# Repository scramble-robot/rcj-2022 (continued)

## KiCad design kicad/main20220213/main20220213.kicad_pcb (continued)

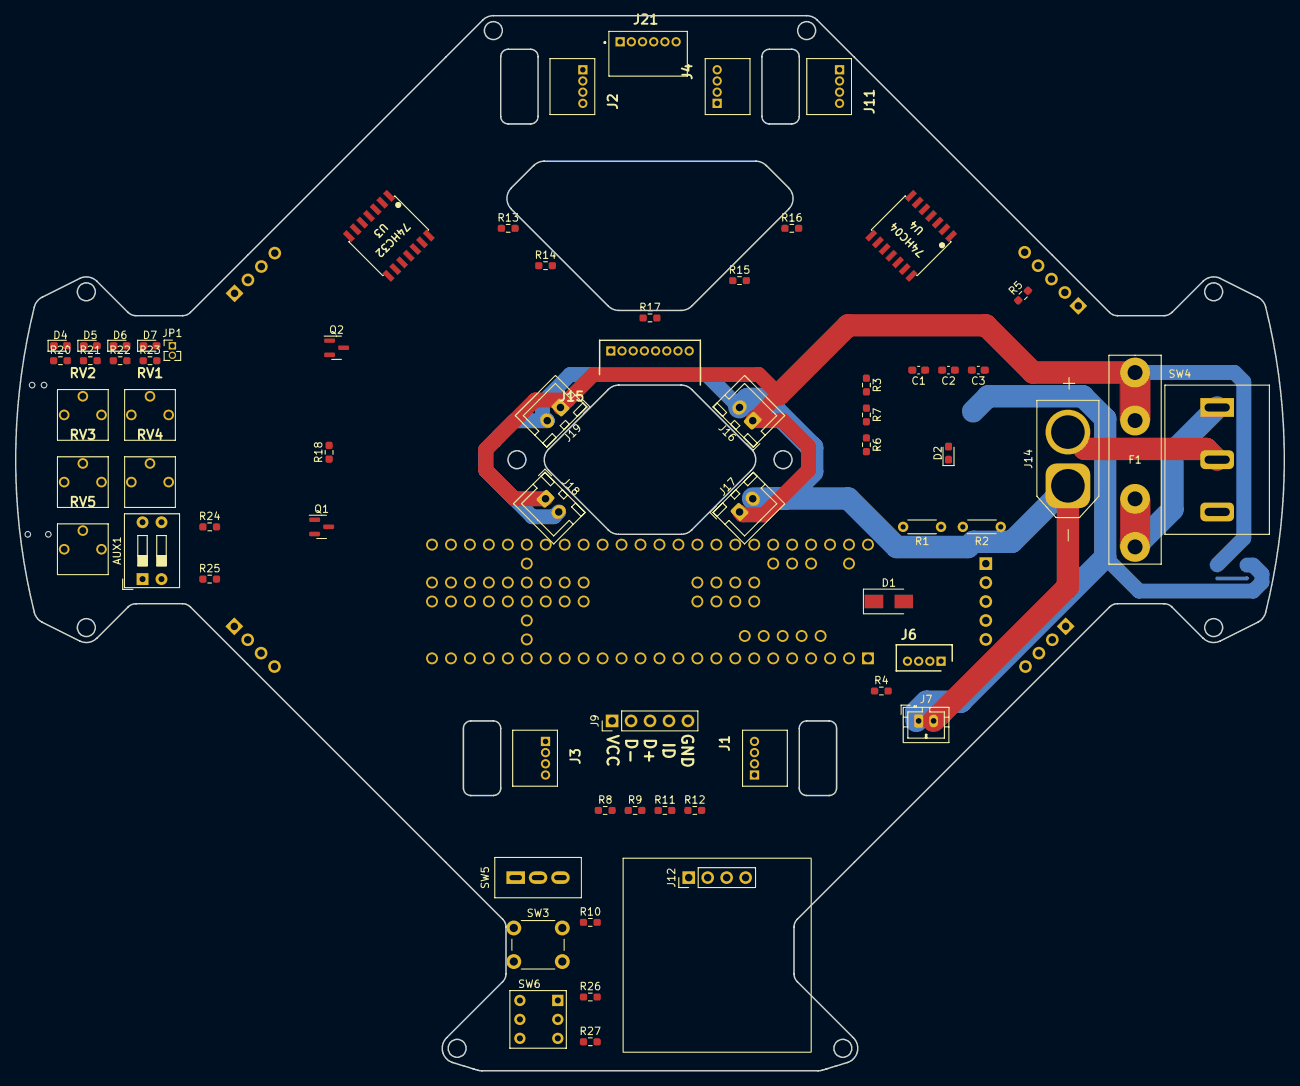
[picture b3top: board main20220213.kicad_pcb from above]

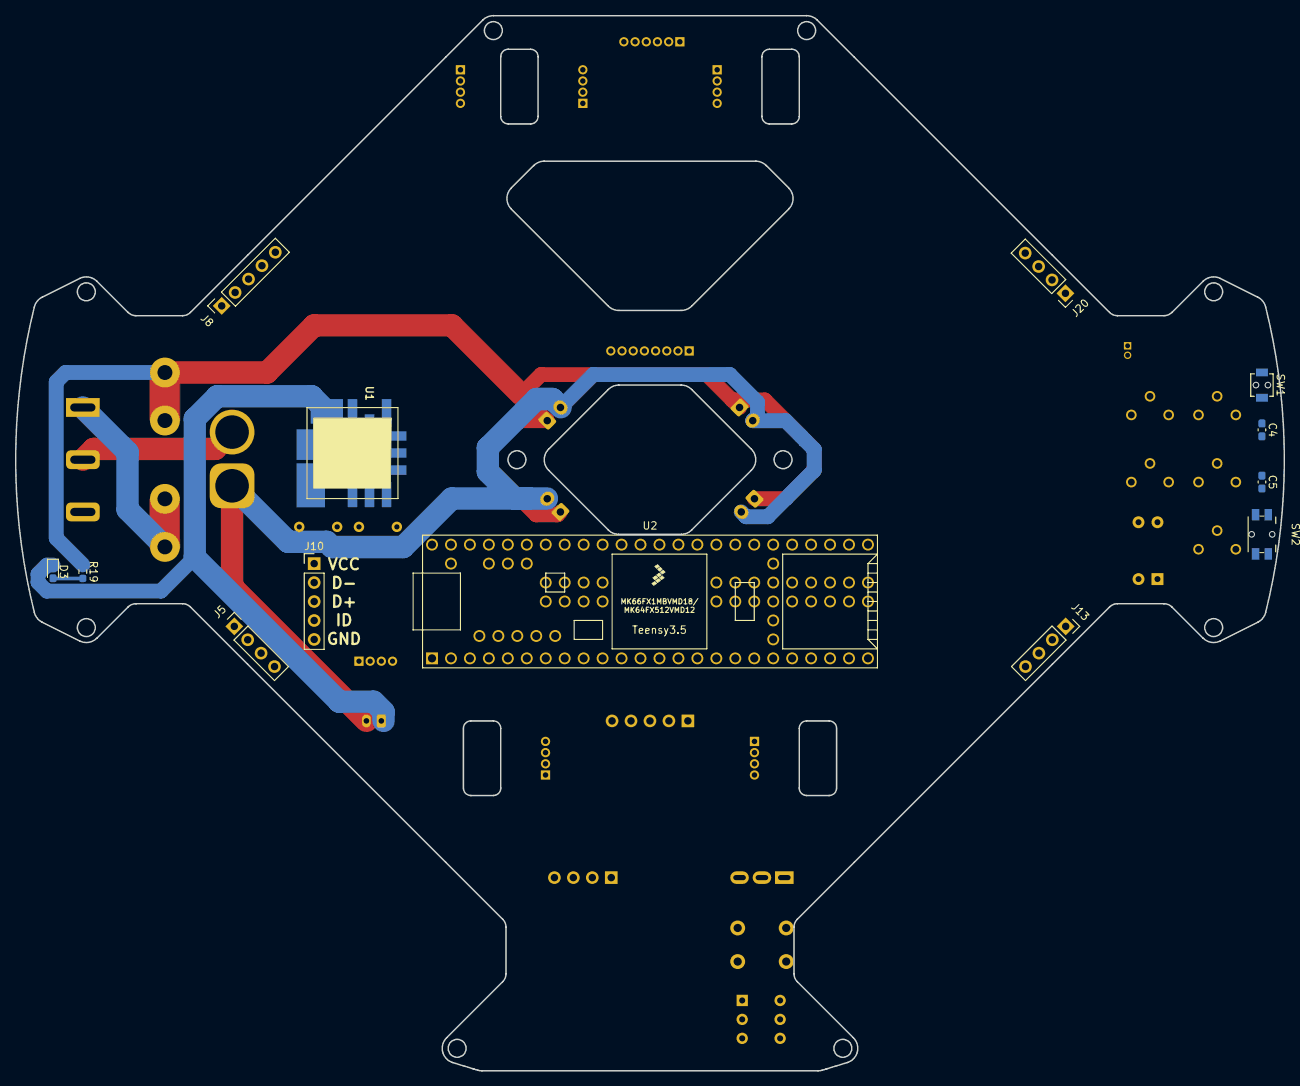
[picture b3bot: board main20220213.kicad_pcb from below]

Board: 2 copper layers, 170.0 x 141.4 mm, 80 parts (13 on the bottom side), 89 nets.

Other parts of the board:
D4: LED1_R; LED_SMLE13WBC8W1
D5: LED2_G; LED_SMLE13WBC8W1
R20, R21, R22, R23: 120; R_0603_1608Metric_Pad0.98x0.95mm_HandSolder

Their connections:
/LED/LED1: R20.1; also elsewhere on the board
/LED/LED2: R21.1; also elsewhere on the board
/LED/LED3: R22.1; also elsewhere on the board
/LED/LED4: R23.1; also elsewhere on the board
unnamed 16: D4.1 (K), D5.1 (K); also elsewhere on the board
unnamed: D4.2 (A), R20.2
unnamed: D5.2 (A), R21.2

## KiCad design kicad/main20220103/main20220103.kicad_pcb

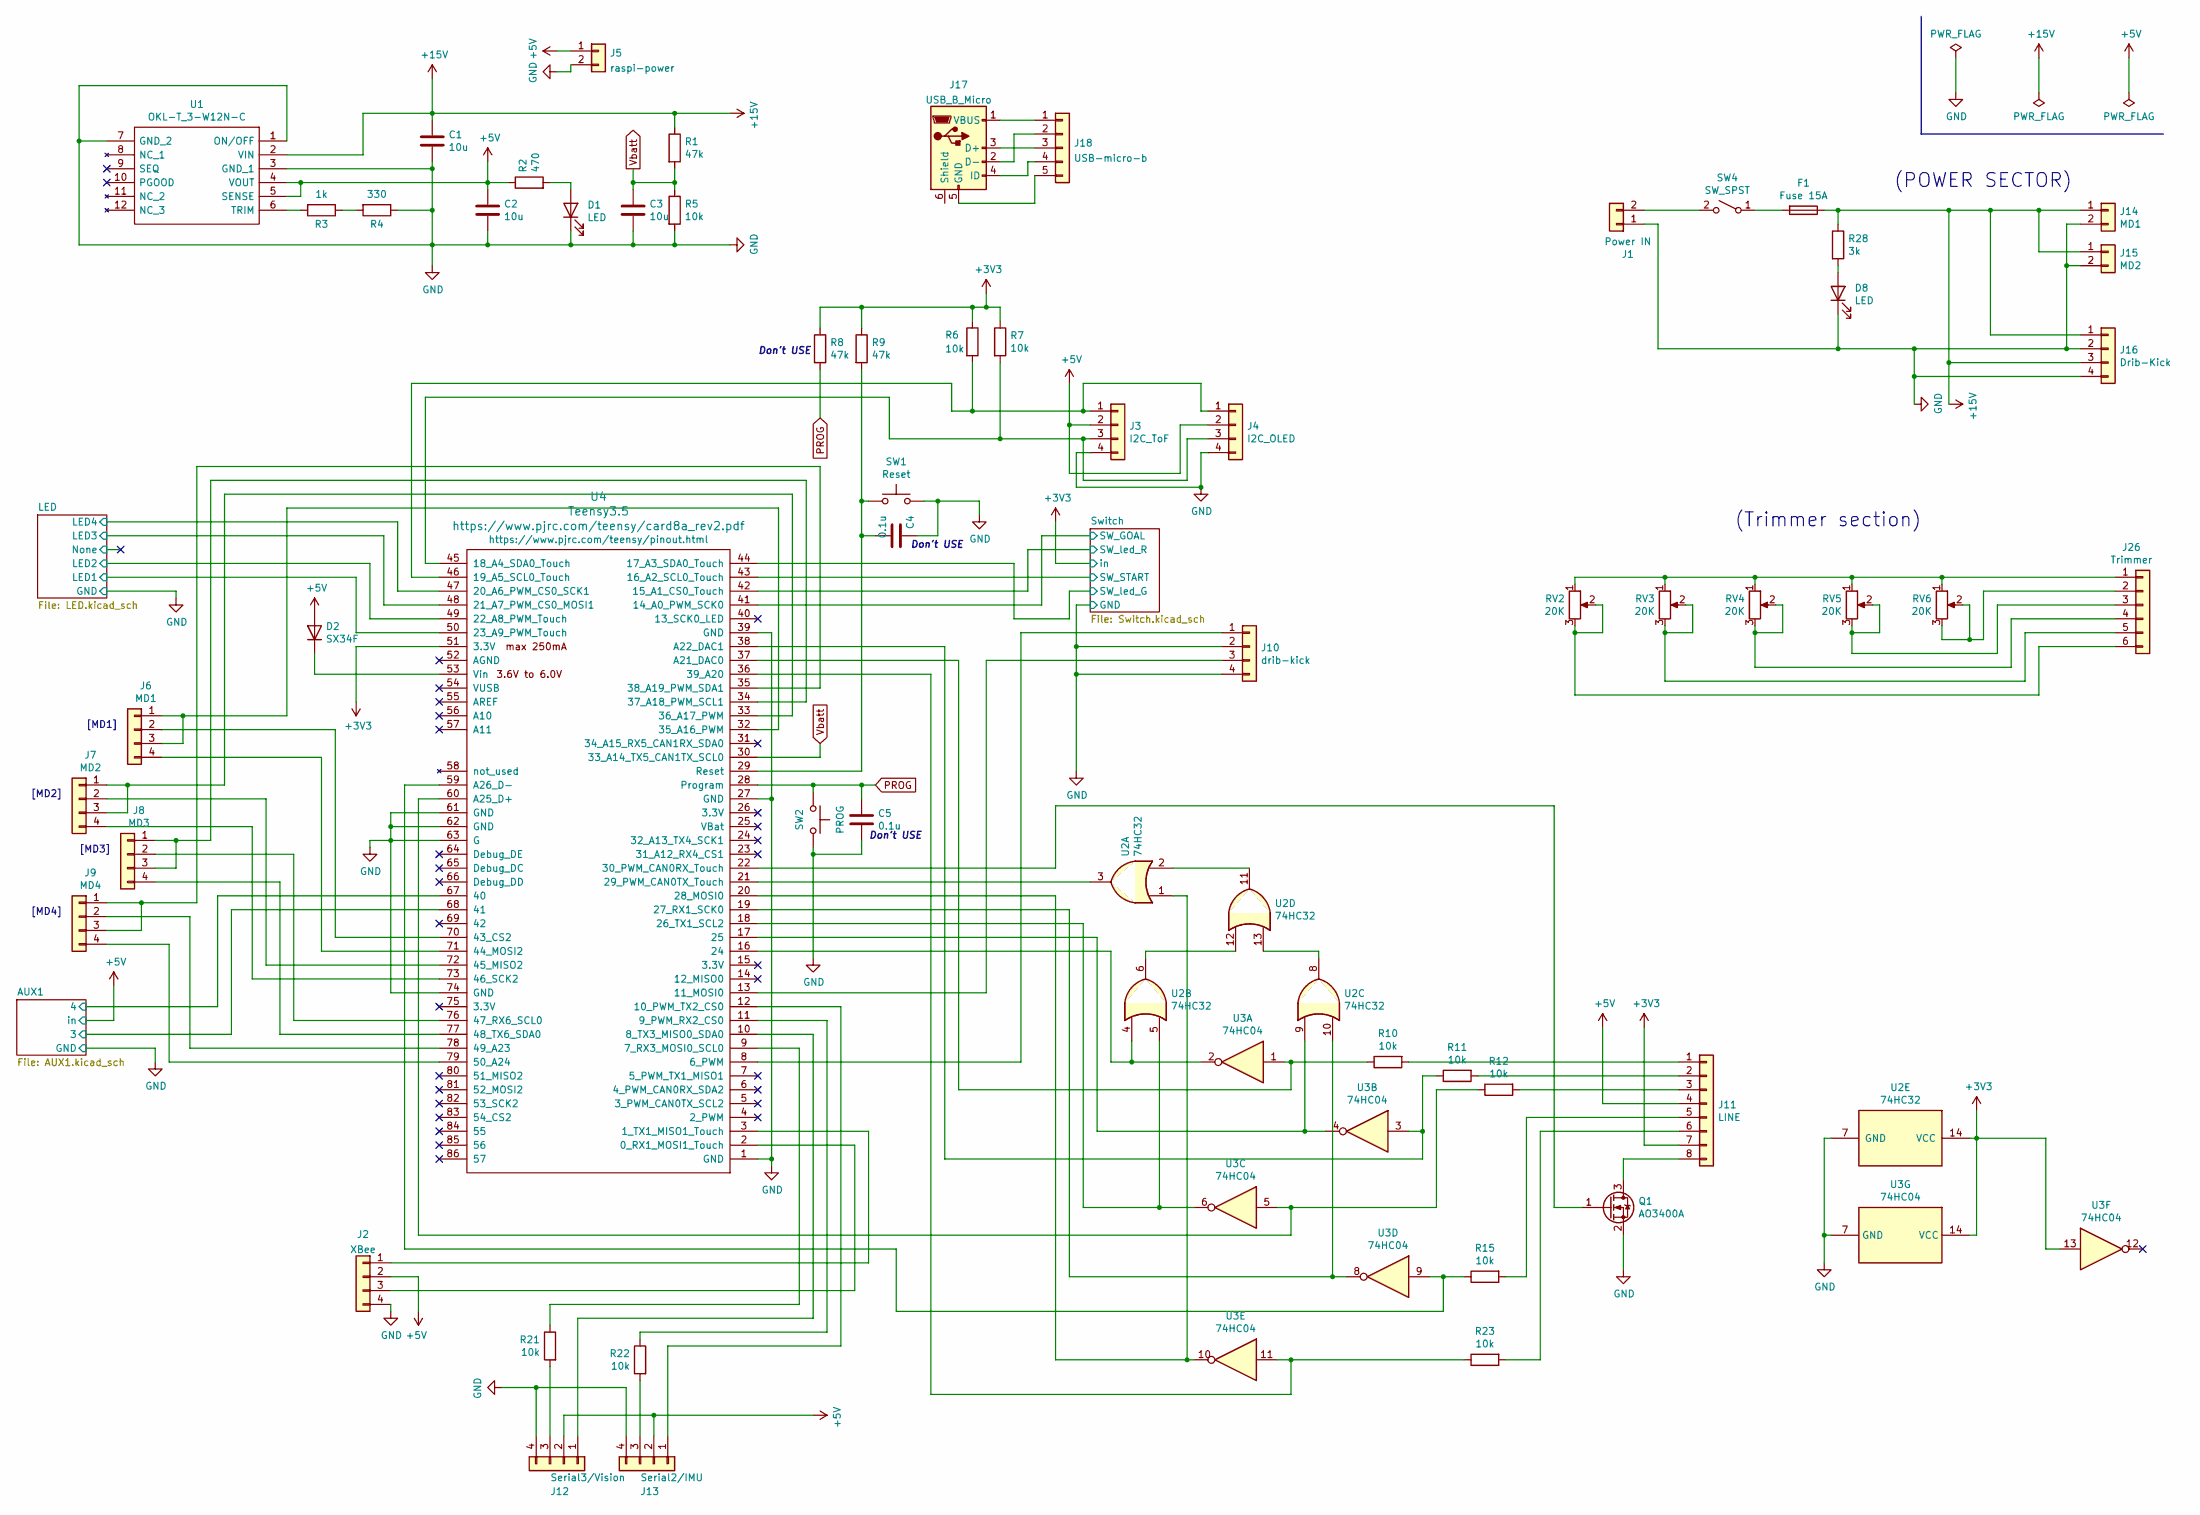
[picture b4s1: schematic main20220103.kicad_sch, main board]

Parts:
C1, C2, C3: 10u; C_0603_1608Metric_Pad1.08x0.95mm_HandSolder
C4, C5: 0.1u; C_0603_1608Metric_Pad1.08x0.95mm_HandSolder
D1, D8: LED; LED_SMLE13WBC8W1
D2: SX34F; D_SMA
F1: Fuse 15A; FUSE_20mm
J1: Power IN; AMASS_XT60-M_1x02_P7.20mm_Vertical
J2: XBee; PinSocket_1x04_P2.54mm_Vertical
J3: I2C_ToF; JSTB4B-ZR
J4: I2C_OLED; OLED
J5: raspi-power; JST_PH_B2B-PH-K_1x02_P2.00mm_Vertical
J6: MD1; JSTB4B-ZR
J7: MD2; JSTB4B-ZR
J8: MD3; JSTB4B-ZR
J9: MD4; JSTB4B-ZR
J10: drib-kick; PinSocket_1x04_P2.54mm_Vertical
J11: LINE; JSTB8B-ZR
J12: Serial3/Vision; JSTB4B-ZR
J13: Serial2/IMU; PinSocket_1x04_P2.54mm_Vertical
J14: MD1; JST_XH_B2B-XH-A_1x02_P2.50mm_Vertical
J15: MD2; JST_XH_B2B-XH-A_1x02_P2.50mm_Vertical
J16: Drib-Kick; PinSocket_1x04_P2.54mm_Vertical
J17: USB_B_Micro; USB_Micro-B_Wuerth_614105150721_Vertical
J18: USB-micro-b; PinHeader_1x05_P2.54mm_Vertical
J26: Trimmer; JSTS6B-ZRLFSN
Q1: AO3400A; SOT-23_Handsoldering
R1, R8, R9: 47k; R_0603_1608Metric_Pad0.98x0.95mm_HandSolder
R2: 470; R_0603_1608Metric_Pad0.98x0.95mm_HandSolder
R3: 1k; R_Axial_DIN0204_L3.6mm_D1.6mm_P5.08mm_Horizontal
R4: 330; R_Axial_DIN0204_L3.6mm_D1.6mm_P5.08mm_Horizontal
R5, R6, R7, R10, R11, R12, R15, R21, R22, R23: 10k; R_0603_1608Metric_Pad0.98x0.95mm_HandSolder
R28: 3k; R_0603_1608Metric_Pad0.98x0.95mm_HandSolder
RV2, RV3, RV4, RV5, RV6: 20K; Trim-GF063P
SW1: Reset; THAU13-AB-R
SW2: PROG; TVAF06-A020B-R
SW4: SW_SPST; SW_SPST_POWER
U1: OKL-T_3-W12N-C; OKL-T3-W12N-C; Manufacturer_Part_Number OKL-T/6-W12N-C; Mouser Part Number 580-OKL-T/6-W12N-C
U2: 74HC32; SOP14W
U3: 74HC04; SOP14W
U4: Teensy3.5; Teensy35_36_x

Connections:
+3V3: J11.7, R6.1, R7.1, R8.1, R9.1, U2.14 (VCC), U3.13, U3.14 (VCC), U4.51 (3.3V); also elsewhere on the board
+5V: C2.1, D2.2 (A), J2.2, J3.2, J4.2, J5.1, J11.4, J12.2, J13.2, R2.1, U1.4 (VOUT), U1.5 (SENSE); also elsewhere on the board
+15V: C1.1, F1.1, J14.1, J15.1, J16.1, J16.3, R1.1, R28.1, U1.2 (VIN)
/AUX1/3: U4.68 (41); also elsewhere on the board
/AUX1/4: U4.67 (40); also elsewhere on the board
/LED/LED1: U4.50 (23_A9_PWM_Touch); also elsewhere on the board
/LED/LED2: U4.49 (22_A8_PWM_Touch); also elsewhere on the board
/LED/LED3: U4.48 (21_A7_PWM_CS0_MOSI1); also elsewhere on the board
/LED/LED4: U4.47 (20_A6_PWM_CS0_SCK1); also elsewhere on the board
/Switch/SW_GOAL: U4.41 (14_A0_PWM_SCK0); also elsewhere on the board
/Switch/SW_START: U4.43 (16_A2_SCL0_Touch); also elsewhere on the board
/Switch/SW_led_G: U4.44 (17_A3_SDA0_Touch); also elsewhere on the board
/Switch/SW_led_R: U4.42 (15_A1_CS0_Touch); also elsewhere on the board
GND: C1.2, C2.2, C3.2, C4.1, C5.2, D1.1 (K), D8.1 (K), J1.1, J2.4, J3.4, J4.4, J5.2, J10.2, J10.4, J12.4, J13.4, J14.2, J15.2, J16.2, J16.4, Q1.2 (S), R4.1, R5.2, SW1.2, SW2.2, U1.1 (ON/OFF), U1.3 (GND_1), U1.7 (GND_2), U2.7 (GND), U3.7 (GND), U4.1 (GND), U4.27 (GND), U4.39 (GND), U4.61 (GND), U4.62 (GND), U4.63 (G), U4.74 (GND); also elsewhere on the board
unnamed: C4.2, R9.2, SW1.1, U4.29 (Reset)
unnamed: D1.2 (A), R2.2
unnamed: D2.1 (K), U4.53 (Vin)
unnamed: D8.2 (A), R28.2
unnamed: F1.2, SW4.1 (A)
unnamed: J1.2, SW4.2 (B)
unnamed: J3.1, J4.1, R6.2, U4.46 (19_A5_SCL0_Touch)
unnamed: J3.3, J4.3, R7.2, U4.45 (18_A4_SDA0_Touch)
unnamed: J6.1, J6.3, U4.32 (35_A16_PWM)
unnamed: J6.2, U4.70 (43_CS2)
unnamed: J6.4, U4.71 (44_MOSI2)
unnamed: J7.1, J7.3, U4.33 (36_A17_PWM)
unnamed: J7.2, U4.72 (45_MISO2)
unnamed: J7.4, U4.73 (46_SCK2)
unnamed: J8.1, J8.3, U4.34 (37_A18_PWM_SCL1)
unnamed: J8.2, U4.76 (47_RX6_SCL0)
unnamed: J8.4, U4.77 (48_TX6_SDA0)
unnamed: J9.1, J9.3, U4.35 (38_A19_PWM_SDA1)
unnamed: J9.2, U4.78 (49_A23)
unnamed: J9.4, U4.79 (50_A24)
unnamed: J10.1, U4.8 (6_PWM)
unnamed: J10.3, U4.13 (11_MOSI0)
unnamed: J11.1, R10.2
unnamed: J11.2, R11.2
unnamed: J11.3, R12.2
unnamed: J11.5, R15.2
unnamed: J11.6, R23.2
unnamed: J11.8, Q1.3 (D)
unnamed: J12.1, U4.10 (8_TX3_MISO0_SDA0)
unnamed: J12.3, R21.2
unnamed: J13.1, U4.12 (10_PWM_TX2_CS0)
unnamed: J13.3, R22.2
unnamed: J17.1 (VBUS), J18.1
unnamed: J17.2 (D-), J18.2
unnamed: J17.3 (D+), J18.3
unnamed: J17.4 (ID), J18.4
unnamed: J17.5 (GND), J18.5
unnamed: J26.1, RV2.1, RV3.1, RV4.1, RV5.1, RV6.1
unnamed: J26.2, RV6.2, RV6.3
unnamed: J26.3, RV5.2, RV5.3
unnamed: J26.4, RV4.2, RV4.3
unnamed: J26.5, RV3.2, RV3.3
unnamed: J26.6, RV2.2, RV2.3
unnamed: Q1.1 (G), U4.22 (30_PWM_CAN0RX_Touch)
unnamed: R3.1, R4.2
unnamed: R3.2, U1.6 (TRIM)
unnamed: R10.1, U3.1, U4.37 (A21_DAC0)
unnamed: R11.1, U3.3, U4.38 (A22_DAC1)
unnamed: R12.1, U3.5, U4.60 (A25_D+)
unnamed: R15.1, U3.9, U4.59 (A26_D-)
unnamed: R21.1, U4.9 (7_RX3_MOSI0_SCL0)
unnamed: R22.1, U4.11 (9_PWM_RX2_CS0)
unnamed: R23.1, U3.11, U4.36 (39_A20)
unnamed: U2.1, U3.10, U4.20 (28_MOSI0)
unnamed: U2.3, U4.21 (29_PWM_CAN0TX_Touch)
unnamed: U2.4, U3.2, U4.16 (24)
unnamed: U2.5, U3.6, U4.18 (26_TX1_SCL2)
unnamed: U2.9, U3.4, U4.17 (25)
unnamed: U2.10, U3.8, U4.19 (27_RX1_SCK0)
unnamed: U2.2, U2.11
unnamed: U2.6, U2.12
unnamed: U2.8, U2.13
unnamed: J2.3, U4.2 (0_RX1_MOSI1_Touch)
unnamed: J2.1, U4.3 (1_TX1_MISO1_Touch)
PROG: C5.1, R8.2, SW2.1, U4.28 (Program)
Vbatt: C3.1, R1.2, R5.1, U4.30 (33_A14_TX5_CAN1TX_SCL0)

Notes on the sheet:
(POWER SECTOR)
(Trimmer section)
Don't USE
[MD3]
[MD2]
[MD1]
[MD4]

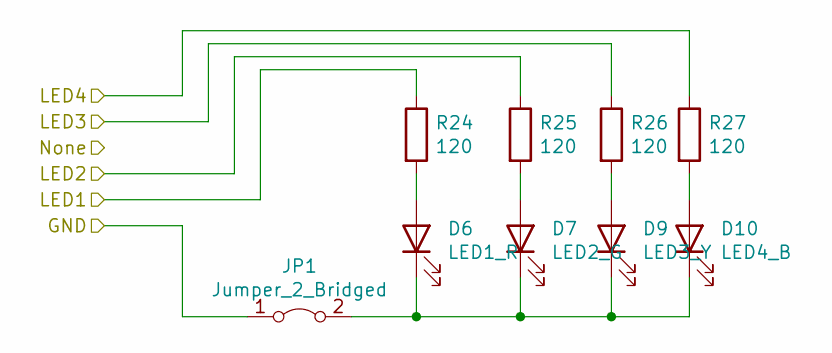
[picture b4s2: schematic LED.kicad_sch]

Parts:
D6: LED1_R; LED_SMLE13WBC8W1
D7: LED2_G; LED_SMLE13WBC8W1
D9: LED3_Y; LED_SMLE13WBC8W1
D10: LED4_B; LED_SMLE13WBC8W1
JP1: Jumper_2_Bridged; PinHeader_1x02_P1.27mm_Vertical
R24, R25, R26, R27: 120; R_0603_1608Metric_Pad0.98x0.95mm_HandSolder

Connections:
/LED/LED1: R24.1; also elsewhere on the board
/LED/LED2: R25.1; also elsewhere on the board
/LED/LED3: R26.1; also elsewhere on the board
/LED/LED4: R27.1; also elsewhere on the board
GND: JP1.1 (A); also elsewhere on the board
unnamed: D6.2 (A), R24.2
unnamed: D7.2 (A), R25.2
unnamed: D9.2 (A), R26.2
unnamed: D6.1 (K), D7.1 (K), D9.1 (K), D10.1 (K), JP1.2 (B)
unnamed: D10.2 (A), R27.2

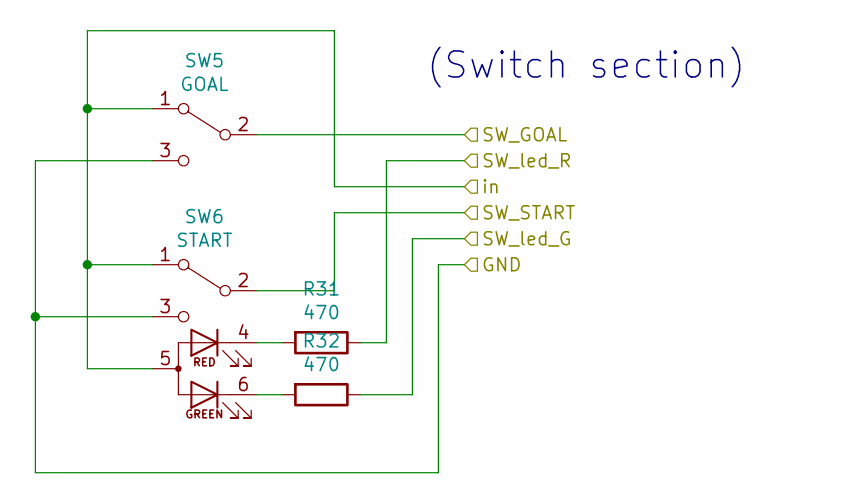
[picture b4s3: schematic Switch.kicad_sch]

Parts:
R31, R32: 470; R_0603_1608Metric_Pad0.98x0.95mm_HandSolder
SW5: GOAL; MFS101D-14-Z
SW6: START; SW_NKK_B-12CCPRM

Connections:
+3V3: SW5.1 (A), SW6.1 (A), SW6.5 (A); also elsewhere on the board
/Switch/SW_GOAL: SW5.2 (B); also elsewhere on the board
/Switch/SW_START: SW6.2 (B); also elsewhere on the board
/Switch/SW_led_G: R32.1; also elsewhere on the board
/Switch/SW_led_R: R31.1; also elsewhere on the board
GND: SW5.3 (C), SW6.3 (C); also elsewhere on the board
unnamed: R31.2, SW6.4 (KR)
unnamed: R32.2, SW6.6 (KG)

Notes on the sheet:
(Switch section)

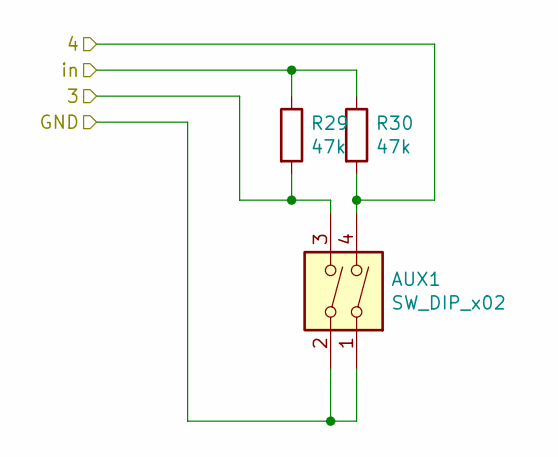
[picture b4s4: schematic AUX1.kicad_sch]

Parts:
AUX1: SW_DIP_x02; SW_DIP_SPSTx02_Slide_9.78x7.26mm_W7.62mm_P2.54mm
R29, R30: 47k; R_0603_1608Metric_Pad0.98x0.95mm_HandSolder

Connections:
+5V: R29.1, R30.1; also elsewhere on the board
/AUX1/3: AUX1.3, R29.2; also elsewhere on the board
/AUX1/4: AUX1.4, R30.2; also elsewhere on the board
GND: AUX1.1, AUX1.2; also elsewhere on the board

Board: 2 copper layers, 74 parts (21 on the bottom side), 87 nets, no tracks yet.

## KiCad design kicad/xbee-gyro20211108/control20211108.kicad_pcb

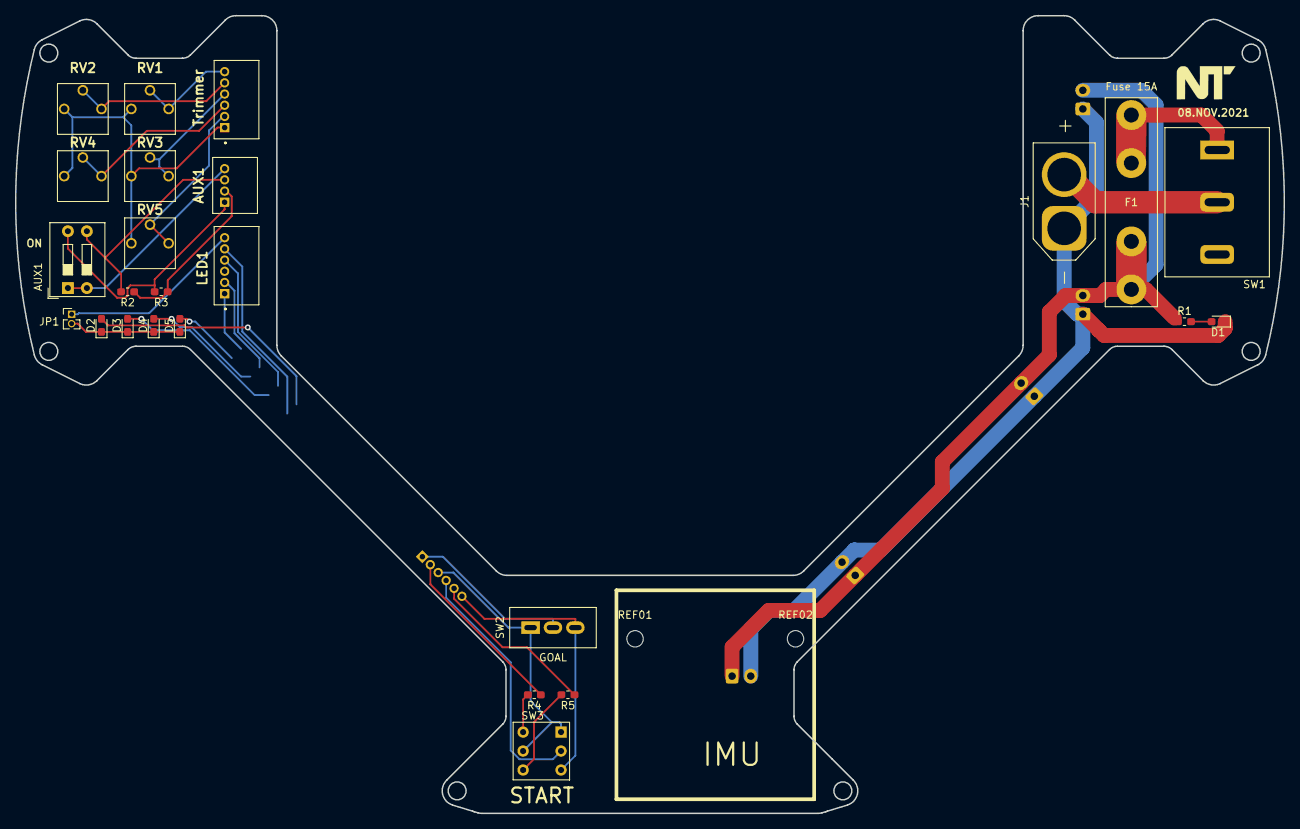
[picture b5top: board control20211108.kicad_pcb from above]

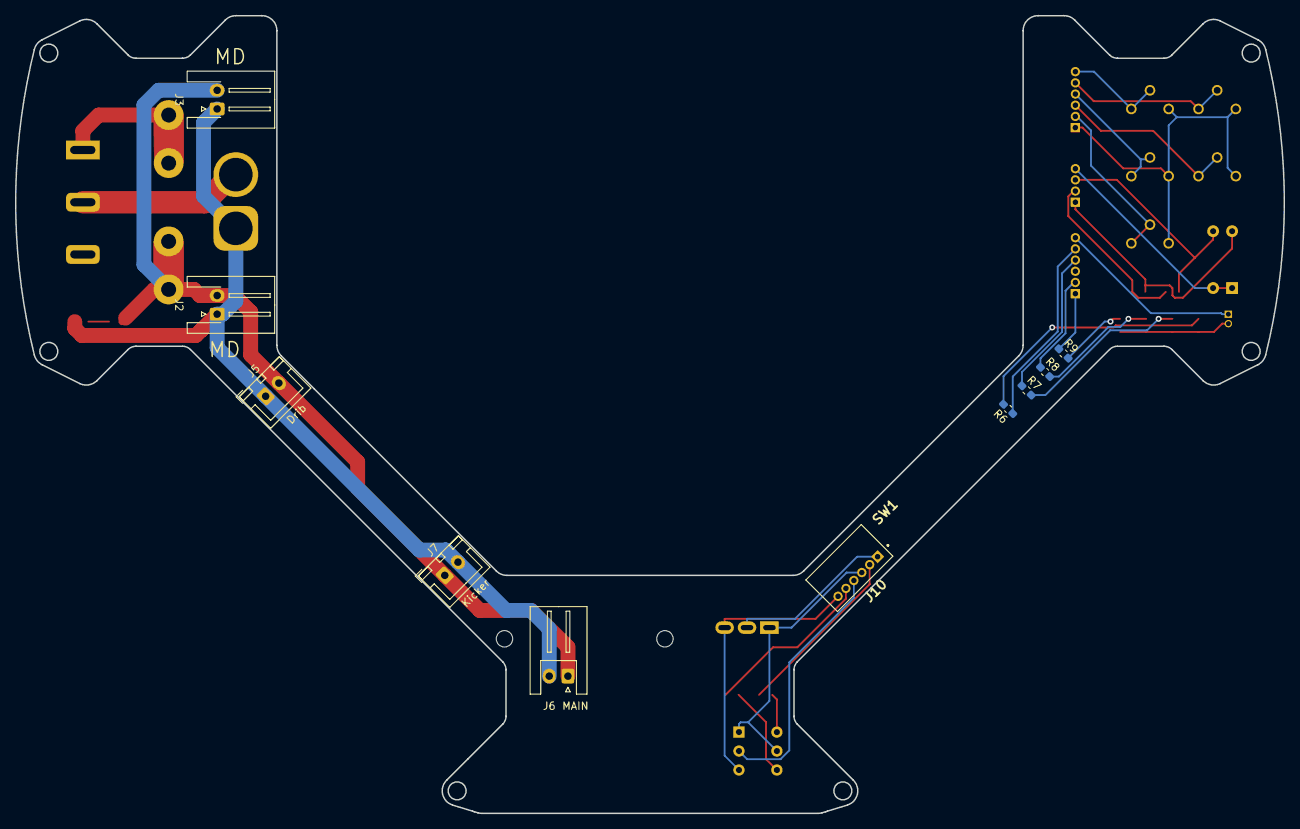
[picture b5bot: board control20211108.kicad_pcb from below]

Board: 2 copper layers, 170.0 x 106.9 mm, 37 parts (10 on the bottom side), 33 nets.

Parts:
AUX1: SW_DIP_x02; SW_DIP_SPSTx02_Slide_9.78x7.26mm_W7.62mm_P2.54mm
D1: LED; LED_SMLE13WBC8W1
D2: LED1_R; LED_SMLE13WBC8W1
D3: LED2_G; LED_SMLE13WBC8W1
D4: LED3_Y; LED_SMLE13WBC8W1
D5: LED4_B; LED_SMLE13WBC8W1
F1: Fuse 15A; FUSE_20mm
J1: Power IN1; AMASS_XT60-M_1x02_P7.20mm_Vertical
J2: MD1; JST_XH_S2B-XH-A-1_1x02_P2.50mm_Horizontal
J3: MD2; JST_XH_S2B-XH-A-1_1x02_P2.50mm_Horizontal
J4: LED1; JSTS6B-ZRLFSN
J5: Drib; JST_XH_B2B-XH-A_1x02_P2.50mm_Vertical
J6: MAIN; JST_XH_S2B-XH-A_1x02_P2.50mm_Horizontal
J7: Kicker; JST_XH_B2B-XH-A_1x02_P2.50mm_Vertical
J8: Trimmer; JSTS6B-ZRLFSN
J9: AUX1; JSTS4B-ZRLFSN
J10: SW1; JSTS6B-ZRLFSN
JP1: Jumper_2_Bridged; PinHeader_1x02_P1.27mm_Vertical
R1: 3k; R_0603_1608Metric_Pad1.05x0.95mm_HandSolder
R2, R3: 47k; R_0603_1608Metric_Pad1.05x0.95mm_HandSolder
R4, R5: 470; R_0603_1608Metric_Pad1.05x0.95mm_HandSolder
R6, R7, R8, R9: 120; R_0603_1608Metric_Pad1.05x0.95mm_HandSolder
REF01, REF02: MountingHole_2.2mm_M2
RV1, RV2, RV3, RV4, RV5: 20K; Trim-GF063P
SW1: SW_SPST; SW_SPST_POWER
SW2: GOAL; MFS101D-14-Z
SW3: START; SW_NKK_B-12CCPRM

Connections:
GND: J10.6, SW2.3, SW3.3
unnamed: AUX1.1, AUX1.2, J9.4
unnamed: AUX1.3, J9.3, R2.2
unnamed: AUX1.4, J9.1, R3.2
unnamed: D1.1, J1.1, J2.1, J3.1, J5.1, J6.2, J7.2
unnamed: D1.2, R1.2
unnamed: D2.1, D3.1, D4.1, D5.1, JP1.2
unnamed: D2.2, R6.2
unnamed: D3.2, R7.2
unnamed: D4.2, R8.2
unnamed: D5.2, R9.2
unnamed: F1.1, J2.2, J3.2, J5.2, J6.1, J7.1, R1.1
unnamed: F1.2, SW1.1
unnamed: J1.2, SW1.2
unnamed: J4.1, R9.1
unnamed: J4.2, R8.1
unnamed: J4.4, R7.1
unnamed: J4.5, R6.1
unnamed: J4.6, JP1.1
unnamed: J8.1, RV1.1, RV2.1, RV3.1, RV4.1, RV5.1
unnamed: J8.2, RV5.2, RV5.3
unnamed: J8.3, RV4.2, RV4.3
unnamed: J8.4, RV3.2, RV3.3
unnamed: J8.5, RV2.2, RV2.3
unnamed: J8.6, RV1.2, RV1.3
unnamed: J9.2, R2.1, R3.1
unnamed: J10.1, SW2.2
unnamed: J10.2, R4.1
unnamed: J10.3, SW2.1, SW3.1, SW3.5
unnamed: J10.4, SW3.2
unnamed: J10.5, R5.1
unnamed: R4.2, SW3.4
unnamed: R5.2, SW3.6

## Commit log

2021-12-28 hajime
2021-12-28 no message
2022-02-02 vision
2022-02-02 neme
2022-02-02 最初の第一歩
2022-02-02 京滋奈まで
2022-02-02 階層変更
2022-02-02 beta
2022-02-06 kicad
2022-02-07 あわせたやつ
2022-02-26 iicad
2022-02-26 自作途中
2022-02-26 del a
2022-03-17 Kamioto Test Push
